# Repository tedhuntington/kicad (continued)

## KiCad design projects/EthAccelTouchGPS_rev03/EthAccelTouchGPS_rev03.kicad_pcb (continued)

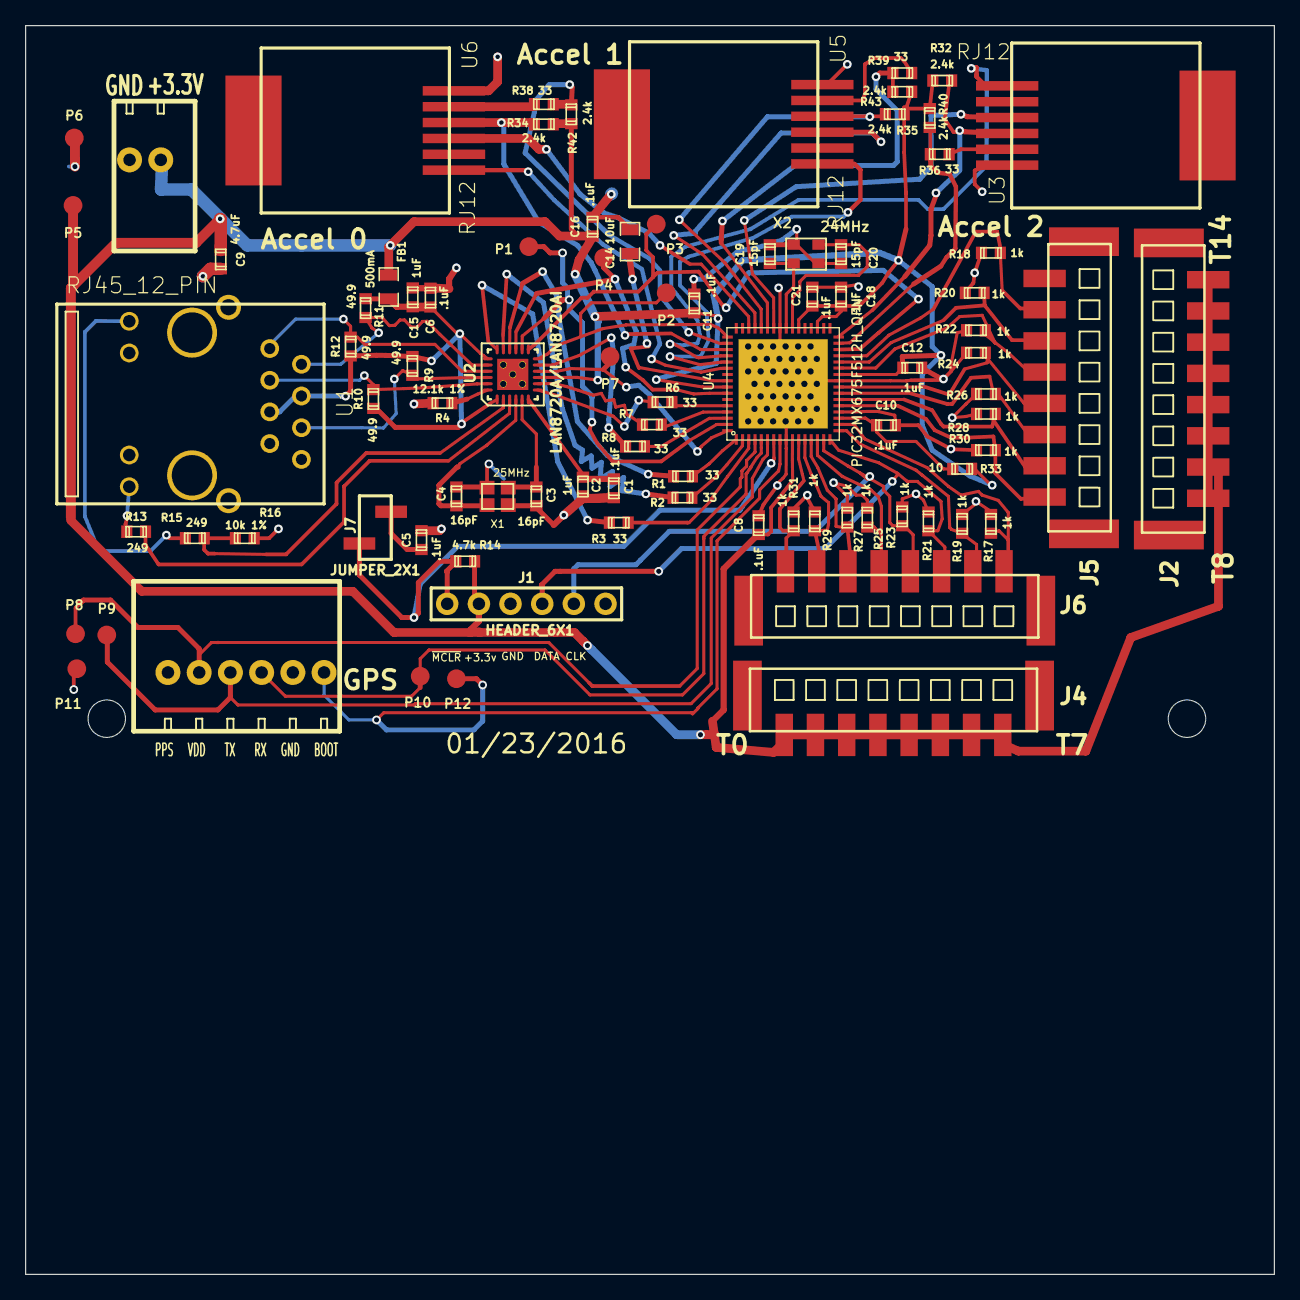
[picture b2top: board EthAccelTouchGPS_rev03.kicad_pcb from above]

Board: 2 copper layers, 100.0 x 100.0 mm, 89 parts (0 on the bottom side), 72 nets.

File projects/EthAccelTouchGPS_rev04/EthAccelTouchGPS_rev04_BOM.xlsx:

EthAccelTouchGPS_rev04
Sat 24 Sep 2016 09:21:54 PM PDT
Eeschema 4.0.3+e1-6302~38~ubuntu14.04.1-stable
Component Count:95
Ref | Qnty | Value | Part | Part# | Unit Cost | Total Cost | Major Distributor | Minor Distributor
C11, C21, C12, C8, C16, C6, C18, C10, C1, C5, C7, | 11 | .1uF | capacitors:SM1608_0603_C | Vj0603V104ZXAPW1BC | 0.1 | 1.1 | Mouser
C13, C14, | 2 | 15pF | capacitors:SM1608_0603_C | GRM1885C1H150JA01D | 0.1 | 0.2 | Mouser
C2, C15, | 2 | 1uF | capacitors:SM1608_0603_C | GRM188R61E105KA12D | 0.1 | 0.2 | Digi-Key
C4, C3, | 2 | 16pF | capacitors:SM1608_0603_C | GRM1885C1H160JA01D | 0.1 | 0.2 | Mouser
C9, | 1 | 4.7uF | capacitors:SM1608_0603_C | C0603C475K9PACTU | 0.13 | 0.13 | Mouser
D1, | 1 | LED | led:SM1206_LED | APTR3216SGC | 0.15 | 0.15 | Mouser
FB1, | 1 | 500mA | resistors:SM0805_R | MPZ2012S601A | 0.12 | 0.12 | Mouser
H1, H2, H3, H4, | 4 | HOLE | holes:Hole_3mm |  | 0 | 0
J1 | 1 | HEADER_6X1 | connectors:HEADER_6x1 | 640456-6 | 0.27 | 0.27 | Mouser
J3, | 1 | TERMINAL_2X1 | connectors:TERMINAL_SPRING_2.54MM_2PIN_1989748 | 1989748 | 0.28 | 0.28 | Mouser
J4, J6, J5, J2, | 4 | TERMINAL_8X1 | connectors:Terminal_8x1_1814760 | 1814760 | 1.31 | 5.24 | Mouser
J7, | 1 | JUMPER_2X1 | connectors:JUMPER_2x1_SMD | M20-8770242 | 0.2 | 0.2 | Mouser
J8 | 1 | HEADER_6X1 | connectors:TERMINAL_SPRING_2.54MM_6PIN_1989780 | 1989780 | 0.77 | 0.77 | Digi-Key/Mouser
P1, P4, P6, P5, P3, P2, P7, P8, P9, P10, P11, P12, | 12 | TEST_PAD | test_pads:TEST_PAD |  | 0 | 0
Q1, | 1 | NMOSFET_GSD | transistors:SOT-23 | 68000-102HLF | 0.36 | 0.36 | Mouser
R14, | 1 | 4.7k | resistors:SM0603_R | ERJ-3EKF4701V | 0.1 | 0.1 | Digi-Key
R15, R13, R5, | 3 | 249 | resistors:SM0603_R | ERJ-2RKF2490X | 0.1 | 0.3 | Mouser/Digi-Key
R16, | 1 | 10k 1% | resistors:SM0603_R | ERJ-3EKF1001V | 0.1 | 0.1 | Digi-Key
R17, R19, R21, R23, R25, R27, R29, R31, R18, R20, R22, R24, R26, R28, R30, | 15 | 1k | resistors:SM0603_R | ERJ-3EKF1002V | 0.1 | 1.5 | Digi-Key
R33, | 1 | 10 | resistors:SM0603_R | CRCW060310R0FKEA | 0.1 | 0.1 | Digi-Key/Mouser
R34, R42, R35, R43, R32, R40, | 6 | 2.4k | resistors:SM0603_R | RC0603FR-072K4L | 0.1 | 0.6 | Digi-Key/Mouser
R37, | 1 | 1M | resistors:SM0603_R | ERJ-3EKF1004V | 0.1 | 0.1 | Digi-Key
R4, | 1 | 12.1k 1% | resistors:SM0603_R | ERJ-6ENF1212V | 0.1 | 0.1 | Mouser
R7, R6, R2, R1, R3, R8, R38, R39, R36, | 9 | 33 | resistors:SM0603_R | RC0603FR-0733RL | 0.1 | 0.9 | Digi-Key/Mouser
R9, R10, R11, R12, | 4 | 49.9 | resistors:SM0603_R | ERJ-3EKF49R9V | 0.1 | 0.4 | Digi-Key
U1, | 1 | RJ45_12_PIN | connectors:RJ45_12pin_Top | HR911105A | 0.85 | 0.85 |  | AliExpress
U2, | 1 | LAN8720A/LAN8720AI | ICs:QFN24+1 | LAN8720A | 1.49 | 1.49 | Digi-Key
U4, | 1 | PIC32MZ0512EFE064_QFN | ICs:QFN64+1H | PIC32MZ0512EFE064-I/MR | 7.86 | 7.86 | MicrochipDirect
U6, U5, U3, | 3 | RJ12 | connectors:RJ12_855135002 | 855135002 | 0.98 | 2.94 | Mouser
X1, | 1 | 25MHz | crystals:crystal_FA-20H | FA-20H 25.0000MF20X-K3 | 0.73 | 0.73 | Mouser
X2, | 1 | 24MHz | crystals:crystal_TSX3225 | TSX-3225 24.0000MF20G-AC3 | 0.51 | 0.51 | Mouser
Total |  |  |  |  |  | 27.8

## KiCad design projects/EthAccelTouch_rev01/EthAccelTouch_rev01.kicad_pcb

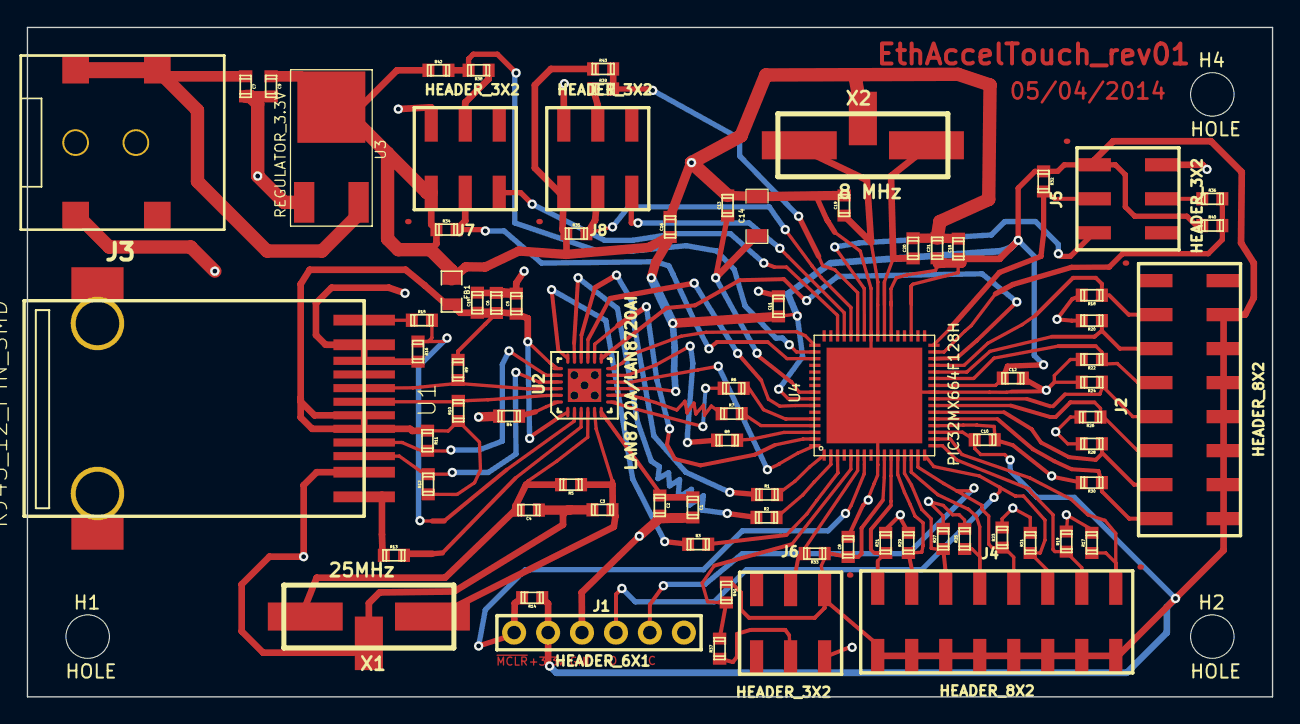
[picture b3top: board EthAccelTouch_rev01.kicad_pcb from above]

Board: 2 copper layers, 93.0 x 50.0 mm, 81 parts (0 on the bottom side), 67 nets.

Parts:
C1, C5, C6, C8, C10, C11, C12, C13, C16, C18, C21: .1uF; TED_SM0603
C2, C15: 1uF; TED_SM0603
C3, C4, C19, C20: 18pF; TED_SM0603
C7, C9: 4.7uF; TED_SM0603
C14: 10uF; TED_SM1206
FB1: 500mA; TED_SM0805
H1, H2, H4: HOLE; TED_Hole_3.25mm
J1: HEADER_6X1; TED_HEADER_6x1_BOTTOM
J2, J4: HEADER_8X2; TED_HEADER_8x2_SMT
J3: Logic DC_2.1MM; TED_DC_2.1mm_SMT
J5, J6, J7, J8: HEADER_3X2; TED_HEADER_3x2_SMT
R1, R2, R3, R6, R7, R8, R36, R37, R38, R39: 33; TED_SM0603
R4: 12.1k 1%; TED_SM0603
R5: 1M; TED_SM0603
R9, R10, R11, R12: 49.9; TED_SM0603
R13, R15: 249; TED_SM0603
R14: 4.7k; TED_SM0603
R16: 10k 1%; TED_SM0603
R17, R18, R19, R20, R21, R22, R23, R24, R25, R26, R27, R28, R29, R30, R31: 1k; TED_SM0603
R32, R33, R34, R35, R40, R41, R42, R43: 2.4k; TED_SM0603
U1: RJ45_12_PIN_SMD; TED_RJ45_12pin_SMD
U2: LAN8720A/LAN8720AI; TED_QFN24
U3: REGULATOR_3.3V; TED_3v_DPAK
U4: PIC32MX664F128H; TED_QFN64+1
X1: 25MHz; TED_crystal_W_GND_SMT_13x5mm
X2: 8 MHz; TED_crystal_W_GND_SMT_13x5mm

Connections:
+3.3v: C8.1, C9.1, C10.1, C11.1, C12.1, C16.1, C18.1, C21.1, FB1.1, J1.2, J2.9, J2.10, J2.11, J2.12, J2.13, J2.14, J2.15, J4.9, J4.10, J4.11, J4.12, J4.13, J4.14, J4.15, J4.16, J5.1, J6.1, J7.1, J8.1, R14.1, R32.1, R33.1, R34.1, R35.1, R40.1, R41.1, R42.1, R43.1, U2.9, U3.2, U4.10, U4.19, U4.26, U4.35, U4.38, U4.57
+5v: C7.1, J3.1, U3.3
AVDD: C5.1, C6.1, C15.1, FB1.2, R9.1, R10.1, R11.1, R12.1, U1.5, U1.6, U2.1, U2.19
ECRSDV: R8.2, U4.62
EMDC: U2.13, U4.30
EMDIO: U2.12, U4.49
EREFCLK: U2.14, U4.63
ERXD0: R7.2, U4.61
ERXD1: R6.2, U4.60
ERXERR: U2.10, U4.64
ETXD0: R2.2, U4.2
ETXD1: R3.2, U4.3
ETXEN: R1.2, U4.1
GND: C1.2, C2.2, C3.1, C4.1, C5.2, C6.2, C7.2, C8.2, C9.2, C10.2, C11.2, C12.2, C13.2, C14.2, C15.2, C16.2, C18.2, C19.2, C20.2, C21.2, J1.3, J3.2, J5.6, J6.6, J7.6, J8.6, R4.2, R16.2, R17.2, R18.2, R19.2, R20.2, R21.2, R22.2, R23.2, R24.2, R25.2, R26.2, R27.2, R28.2, R29.2, R30.2, R31.2, U1.2, U1.10, U1.11, U2.25, U3.1, U4.9, U4.20, U4.25, U4.41, U4.65, X1.3, X2.3
GreenLED: R15.1, U1.12
ICSPCLK_RB1: J1.5, J4.4, R23.1, U4.15
ICSPDAT_RB0: J1.4, J4.3, R21.1, U4.16
INT0: J7.3, U4.46
INT1: J5.3, U4.42
INT4: J8.3, U4.45
unnamed: C3.2, R5.1, U2.5, X1.1
unnamed: C4.2, R5.2, U2.4, X1.2
unnamed: R8.1, U2.11
unnamed: R3.1, U2.18
unnamed: R2.1, U2.17
unnamed: R1.1, U2.16
unnamed: R13.2, U2.3
unnamed: R15.2, R16.1, U2.2
unnamed: R4.1, U2.24
unnamed: R7.1, U2.8
unnamed: R6.1, U2.7
unnamed: C19.1, U4.40, X2.1
unnamed: C1.1, C2.1, U2.6
unnamed: C13.1, C14.1, U4.56
unnamed: C20.1, U4.39, X2.2
unnamed: J8.5, R39.1
unnamed: J7.5, R38.1
unnamed: J6.5, R37.1
unnamed: J5.5, R36.1
RB2: J4.5, R25.1, U4.14
RB3: J4.6, R27.1, U4.13
RB4: J4.7, R29.1, U4.12
RB5: J4.8, R31.1, U4.11
RB6: J4.2, R19.1, U4.17
RB7: J4.1, R17.1, U4.18
RB8: J2.8, R30.1, U4.21
RB9: J2.7, R28.1, U4.22
RB10: J2.6, R26.1, U4.23
RB11: J2.5, R24.1, U4.24
RB12: J2.4, R22.1, U4.27
RB13: J2.3, R20.1, U4.28
RB14: J2.2, R18.1, U4.29
RXN: R9.2, U1.8, U2.22
RXP: R10.2, U1.7, U2.23
SCL1: J8.2, R35.2, U4.44
SCL3: J7.2, R34.2, U4.51
SCL4: J6.2, R33.2, U4.6
SCL5: J5.2, R32.2, U4.32
SDA1: R39.2, R43.2, U4.43
SDA3: R38.2, R42.2, U4.50
SDA4: R37.2, R41.2, U4.5
SDA5: R36.2, R40.2, U4.31
TXN: R11.2, U1.4, U2.20
TXP: R12.2, U1.3, U2.21
YellowLED: R13.1, U1.1
nRST: U2.15, U4.58
~MCLR~: J1.1, R14.2, U4.7
